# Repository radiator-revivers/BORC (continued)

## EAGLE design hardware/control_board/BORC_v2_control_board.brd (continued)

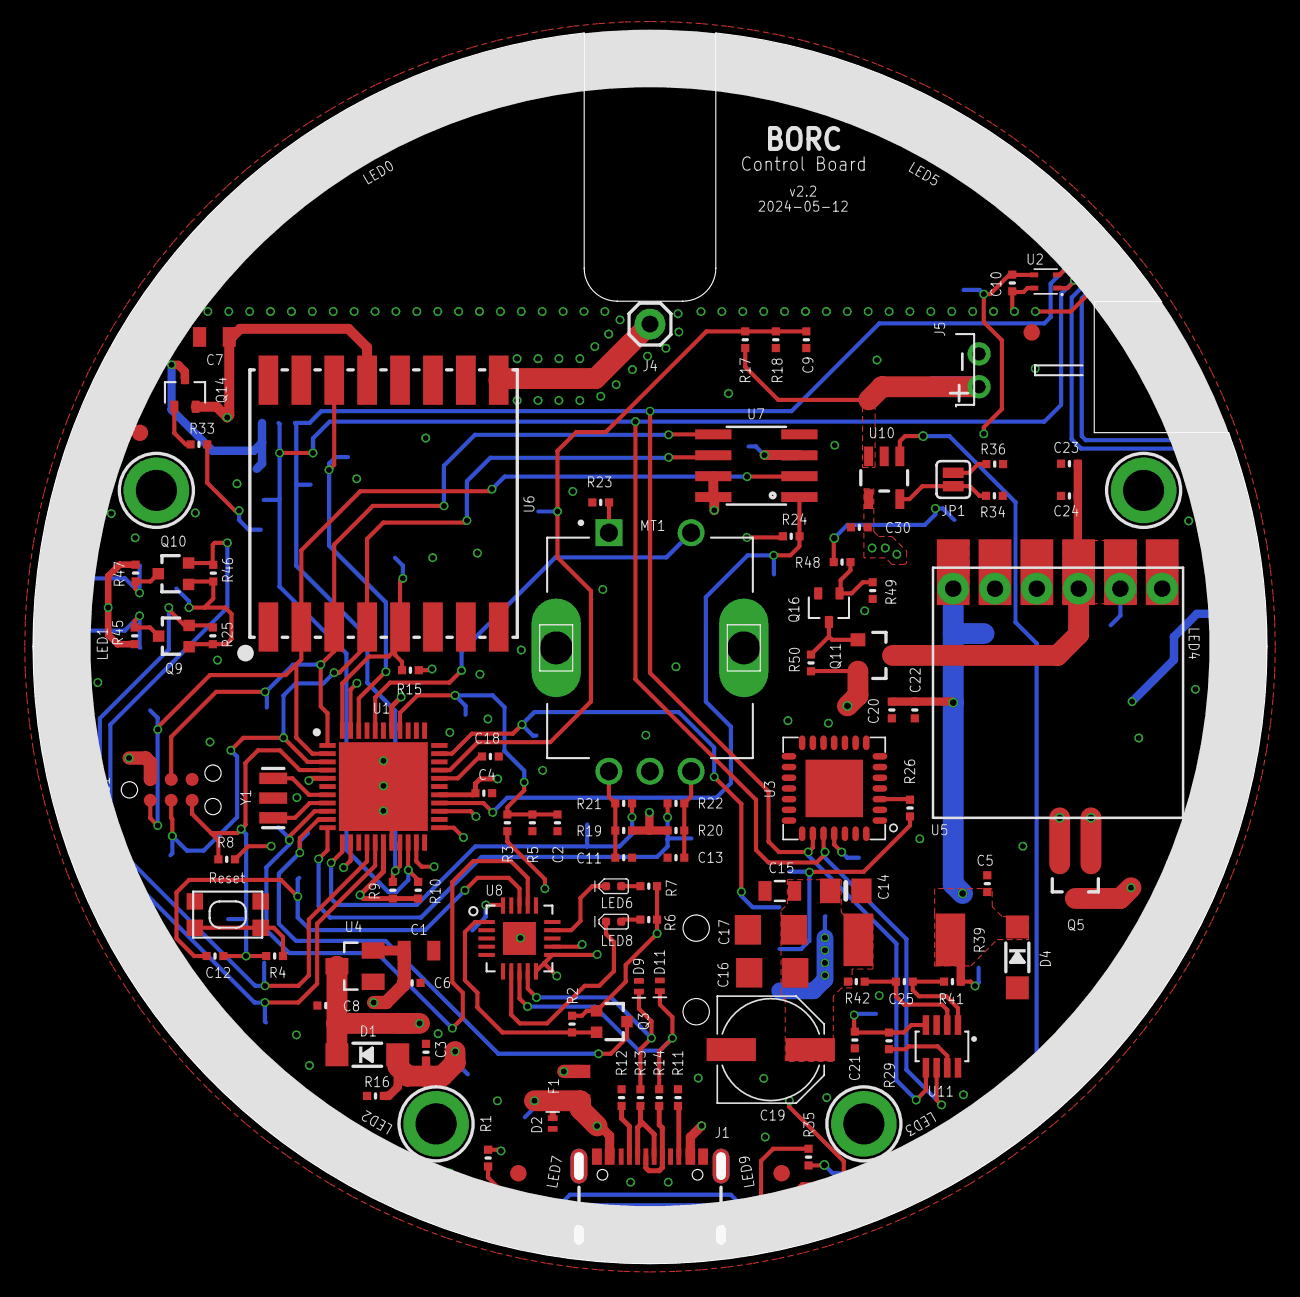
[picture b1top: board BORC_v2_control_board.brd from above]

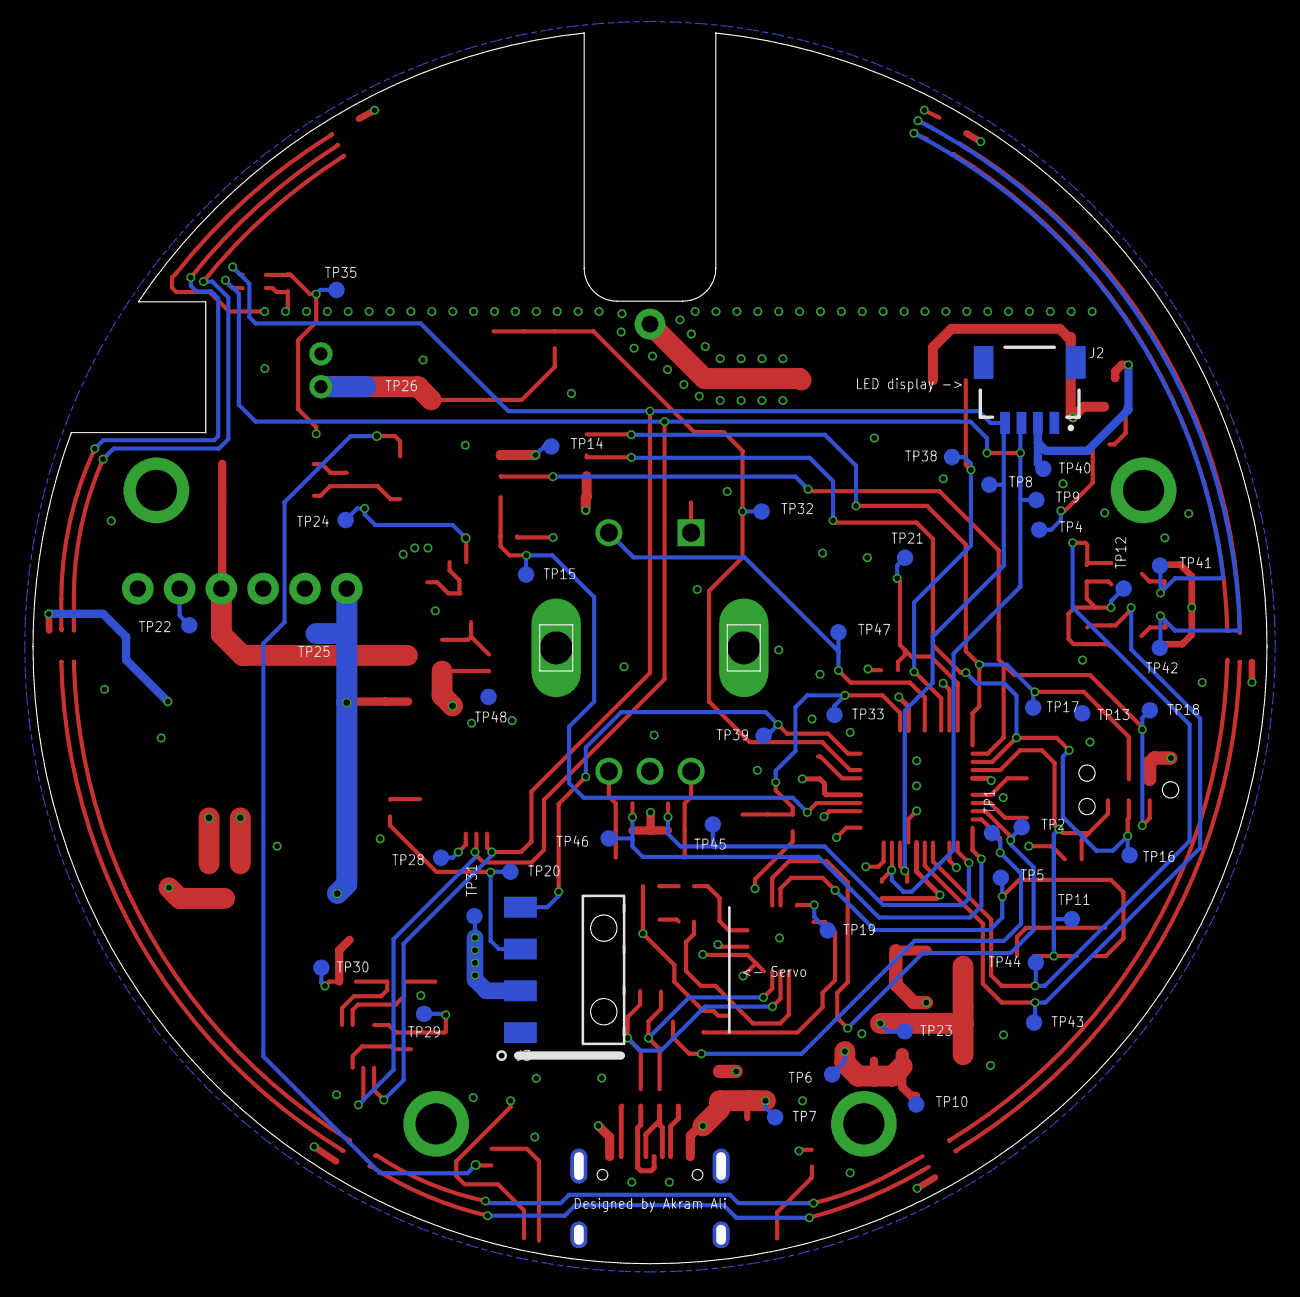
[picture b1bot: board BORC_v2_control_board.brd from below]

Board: 4 copper layers, 74.4 x 74.2 mm, 160 parts (45 on the bottom side), 80 nets.

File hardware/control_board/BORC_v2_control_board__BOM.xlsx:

Parts | Qty | Value | Manufacturer | MPN | Description
J4 | 1 |  |  |  | 915 MHz right angled helical spring antenna, 17.5 mm/0.68", 2.15 dBi gain, 50Ω 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
R39 | 1 | 0.1/1%/2W | Vishay Dale | RCWE2512R100FKEA | 100 mOhms ±1% 2W Chip Resistor 2512 (6432 Metric) Automotive AEC-Q200, Current 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
C14 | 1 | 0.1uF | YAGEO | CC0805KRX7R9BB104 | 0.1 µF ±10% 50V Ceramic Capacitor X7R 0805 (2012 Metric)
C2, C3, C4, C5, C6, C9, C10, C11, C12, C13, C18, C21, C25 | 13 | 0.1uF | Murata Electronics | GRM155R71H104KE14D | 0.1 µF ±10% 50V Ceramic Capacitor X7R 0402 (1005 Metric)
C1, C7 | 2 | 0.33µF | Murata Electronics | GRM219R71H334KA88D | 0.33 µF ±10% 50V Ceramic Capacitor X7R 0805 (2012 Metric)
R41, R42 | 2 | 10 | YAGEO | RC0402FR-0710RL | 10 Ohms ±1% 0.063W, 1/16W Chip Resistor 0402 (1005 Metric) Moisture Resistant T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
R4 | 1 | 100 | YAGEO | RC0402FR-07100RL | 100 Ohms ±1% 0.063W, 1/16W Chip Resistor 0402 (1005 Metric) Moisture Resistant 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
C19 | 1 | 100uF | KEMET | A768EB107M1ELAS036 | 100 µF 25 V Aluminum - Polymer Capacitors Radial, Can - SMD 36mOhm 2000 Hrs @ 1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
R2, R8, R15, R16, R19, R20, R21, R22, R23, R24, R25, R29, R35, R45, R46, R47, R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 | 18 | 10K | YAGEO | RC0402FR-7W10KL | 10 kOhms ±1% 0.125W, 1/8W Chip Resistor 0402 (1005 Metric) Moisture Resistant T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
R3, R5, R17, R18 | 4 | 10M | YAGEO | RC0402FR-0710ML | 10 MOhms ±1% 0.063W, 1/16W Chip Resistor 0402 (1005 Metric) Moisture Resistant 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
C15 | 1 | 10uF | Murata Electronics | GRM21BR61H106KE43L | 10 µF ±10% 50V Ceramic Capacitor X5R 0805 (2012 Metric)
C8, C20, C22, C23, C24, C30 | 5 | 10uF | Murata Electronics | GRM21BR61H106KE43L | 10 µF ±10% 50V Ceramic Capacitor X5R 0805 (2012 Metric)
Y1 | 1 | 16 MHz | Murata Electronics | CSTNE16M0V530000R0 | 16 MHz Ceramic Resonator Built in Capacitor 15 pF ±0.3% 40 Ohms -40°C ~ 85°C Su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
R1, R6, R7, R33, R48 | 5 | 1K | YAGEO | RC0402FR-071KL | 1 kOhms ±1% 0.063W, 1/16W Chip Resistor 0402 (1005 Metric) Moisture Resistant T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
R34, R36 | 2 | 2K | YAGEO | RC0402FR-072KL | 2 kOhms ±1% 0.063W, 1/16W Chip Resistor 0402 (1005 Metric) Moisture Resistant T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
C16, C17 | 2 | 2.2uF | KEMET | C1206C225K5RAC7800 | 2.2 µF ±10% 50V Ceramic Capacitor X7R 1206 (3216 Metric)
R26 | 1 | 220 | YAGEO | RC0402FR-13220RL | 220 Ohms ±1% 0.063W, 1/16W Chip Resistor 0402 (1005 Metric) Moisture Resistant 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
R13, R14 | 2 | 27 | YAGEO | RC0402FR-0727RL | 27 Ohms ±1% 0.063W, 1/16W Chip Resistor 0402 (1005 Metric) Moisture Resistant T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
R9, R10 | 2 | 4.7K | YAGEO | RC0402FR-074K7L | 4.7 kOhms ±1% 0.063W, 1/16W Chip Resistor 0402 (1005 Metric) Moisture Resistant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
R11, R12 | 2 | 5.1K | YAGEO | RC0402FR-135K1L | 5.1 kOhms ±1% 0.063W, 1/16W Chip Resistor 0402 (1005 Metric) Thick Film
F1 | 1 | 6V 1.1A | Bourns Inc. | MF-PSML110/6-2 | Polymeric PTC Resettable Fuse 6V 1.1 A Ih Surface Mount 0805 (2012 Metric), Con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
U6 | 1 | 915MHz | HOPERF | RFM69HCW | HOPERF RFM69H ISM Transceiver Module General ISM 915MHz Surface Mount
LED0, LED1, LED2, LED3, LED4, LED5 | 6 | APA102-2020 | Shenzhen LED Color Opto Electronic CO.,LTD | APA102-2020 | APA102-2020 Super LED/DotStar Pixels
U7 | 1 | W25X40CLSNIG | Winbond Electronics | W25X40CLSNIG | FLASH Memory IC 4Mbit SPI 104 MHz 8-SOIC
U1 | 1 | ATMEGA1284P-MU | Microchip Technology | ATMEGA1284P-MU | AVR AVR® ATmega Microcontroller IC 8-Bit 20MHz 128KB (64K x 16) FLASH 44-VQFN (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
Q3, Q9, Q10 | 3 | BSS138PW,115 | Nexperia USA Inc. | BSS138PW,115 | N-Channel 60 V 320mA (Ta) 260mW (Ta), 830mW (Tc) Surface Mount SOT-323
U8 | 1 | FT231XQ-R | FTDI, Future Technology Devices International Ltd | FT231XQ-R | USB Bridge, USB to UART USB 2.0 UART Interface 20-QFN (4x4)
LED8 | 1 | GREEN | Inolux | IN-S42ATG | Green 525nm LED Indication - Discrete 3.3V 0402 (1005 Metric)
U11 | 1 | INA219AIDCNR | Texas Instruments | INA219AIDCNR | Current Monitor Regulator High-Side 10mA SOT-23-8
J3 | 1 | M20-8900405 | Harwin Inc. | M20-8900405 | Connector Header Surface Mount, Right Angle 4 position 0.100" (2.54mm)
D4 | 1 | 60V, 2A | SMC Diode Solutions | MBR260HW | Diode 60 V 2A Surface Mount SOD-123
D1 | 1 | 40V, 1A | STMicroelectronics | STPS140Z | Diode 40 V 1A Surface Mount SOD-123
U4 | 1 | 3.3V, 250mA | Microchip Technology | MCP1703T-3302E/CB | Linear Voltage Regulator IC Positive Fixed 1 Output 250mA SOT-23A-3
U10 | 1 | MCP73831T-2ACI/OT | Microchip Technology | MCP73831T-2ACI/OT | Charger IC Lithium Ion/Polymer SOT-23-5
U3 | 1 | PCA9685 | NXP USA Inc. | PCA9685BS,118 | LED Driver IC 16 Output Linear PWM Dimming 25mA 28-HVQFN (6x6)
MT1 | 1 | PEC11R-4215F-S0024 | Bourns Inc. | PEC11R-4215F-S0024 | Rotary Encoder Mechanical 24 Quadrature (Incremental) Vertical
U5 | 1 | 4012 | Pololu Corporation | U3V40F5 | Non-Isolated PoL Module DC DC Converter 1 Output 5V 3.5A 1.3V - 5V Input
J2 | 1 | 4 POS 1mm | JST Sales America Inc. | SM04B-SRSS-TB(LF)(SN) | Connector Header Surface Mount, Right Angle 4 position 0.039" (1.00mm)
LED6, LED7 | 2 | RED | Inolux | IN-S42ATR | Red 631nm LED Indication - Discrete 2.1V 0402 (1005 Metric)
J5 | 1 | 2 POS 2.0mm | JST Sales America Inc. | S2B-PH-K-S | Connector Header Through Hole, Right Angle 2 position 0.079" (2.00mm)
U2 | 1 | SHT40-BD1B | Sensirion AG | SHT40-BD1B-R3 | Humidity, Temperature 0 ~ 100% RH I²C ±1.8% RH 6 s Surface Mount
D2, D9, D11 | 3 | SP0402U-ULC-01ETG | Littelfuse Inc. | SP0402U-ULC-01ETG | 9.2V (Typ) Clamp 2A (8/20µs) Ipp Tvs Diode Surface Mount 0402/2DFN (1x0.60)
SW1 | 1 | SPST-NO 50mA 32V | C&K | KMR221GLFS | Tactile Switch SPST-NO Top Actuated Surface Mount
Q5, Q11 | 2 | P-CH 30V 4A SOT23F | Toshiba Semiconductor and Storage | SSM3J374R,LF | P-Channel 30 V 4A (Ta) 1W (Ta) Surface Mount SOT-23F
Q16 | 1 | BJT NPN 40V 0.2A | Rohm Semiconductor | UMT3904T106 | Bipolar (BJT) Transistor NPN 40 V 200 mA 300MHz 200 mW Surface Mount UMT3
Q14 | 1 | BJT PNP 40V 0.2A | Rohm Semiconductor | UMT3906T106 | Bipolar (BJT) Transistor PNP 40 V 200 mA 250MHz 200 mW Surface Mount UMT3
J1 | 1 | CONN RCP USB2.0 TYP C 24P SMD RA | GCT | USB4105-GF-A | USB-C (USB TYPE-C) USB 2.0 Receptacle Connector 24 (16+8 Dummy) Position Surfac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
LED9 | 1 | YELLOW | Inolux | IN-S42ATY | Yellow 592nm LED Indication - Discrete 1.9V 0402 (1005 Metric)

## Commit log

2024-05-08 LED board v2.1 - replaced with 0402 LEDs, arranged in 3x2.5 mm grid, increased width of board to 55 mm
2024-05-08 LED board updated to v2.1
    - Changed 0603 LEDs to 0402
    - Arranged LEDs in grid of 3 x 2.5 mm spacing
    - Increased board width from 50 to 55mm to accommodate spacing
    - Rerouted all traces to LEDs again for new spacing (needs to be verified; v2.0 worked)
    - ERC/DRC done
    - Added BOM
2024-05-12 v2.2 - bug fixes
    - Fixed display power circuit with PNP (active low)
    - Replace charger with MCP73781 (can toggle between 500mA and 1000mA with jumper)
    - Fixed battery JST with PH connector
    - Fixed 5V switch to switch before 5V boost instead of after to avoid voltage drop
    - Merged 5V power with LED power
    - Connected USB shield to ground
